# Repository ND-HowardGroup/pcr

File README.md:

ndPCR
=====

Historical code for ND PCR thermocycler, along with most current generation.

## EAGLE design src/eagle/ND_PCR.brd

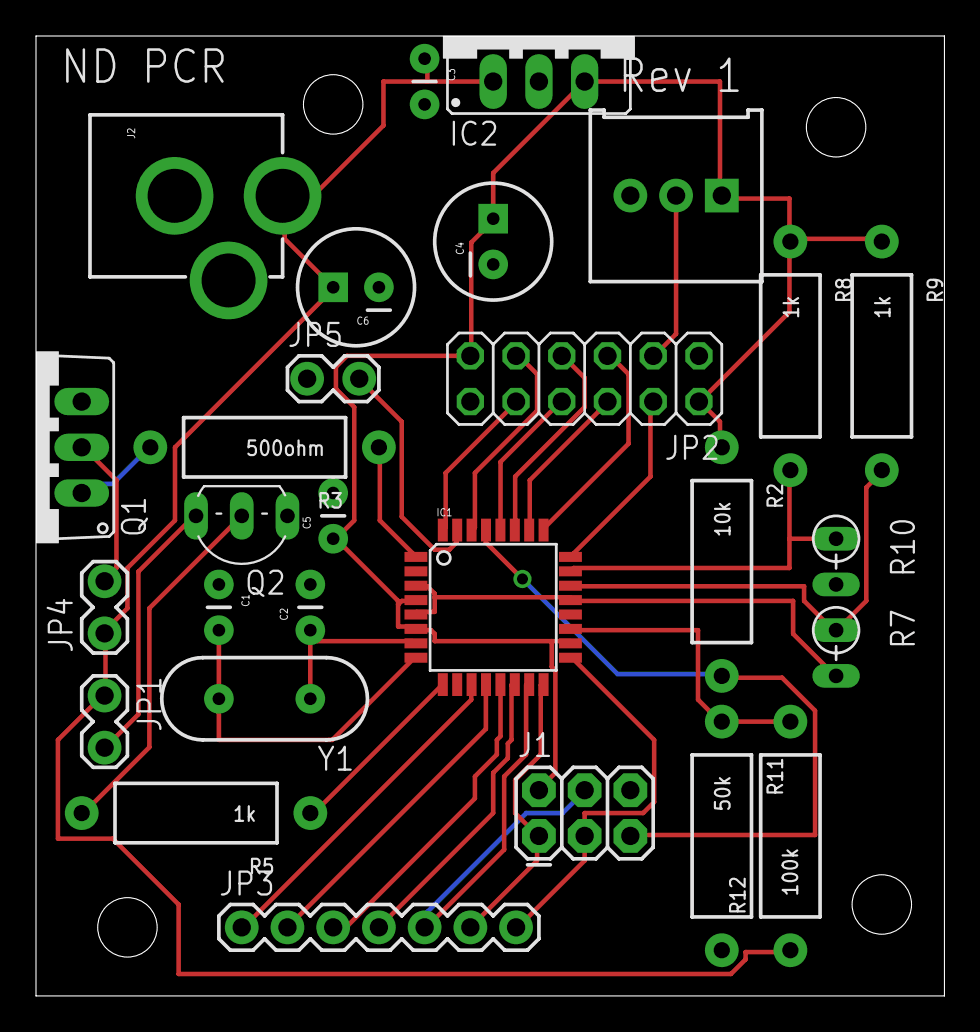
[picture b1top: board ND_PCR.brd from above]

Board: 2 copper layers, 50.5 x 53.3 mm, 32 parts (0 on the bottom side), 31 nets.

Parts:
C1, C2: 20 pF; CAP-PTH-SMALL
C3, C5: 100 nF; CAP-PTH-SMALL
C4, C6: 100 uF; CPOL-RADIAL-100UF-25V
IC1: AVR-MEGA8-AI; TQFP32-08
IC2: 7805; 78XXS
J1: ICSP; 2X3
J2: POWER_JACKPTH; POWER_JACK_PTH
JP1: Fan connector; 1X02_LOCK
JP2: LCD; 2X06
JP3: keypad; 1X07
JP4: 2x 27ohm in ||; 1X02_LOCK
JP5: serial out; 1X02_LOCK
Q1: TIP120TO220V; TO220AV
Q2: 2N2222TO92; TO92-EBC
R2: 10k; AXIAL-0.5
R3: 500ohm; AXIAL-0.5
R5, R8, R9: 1k; AXIAL-0.5
R7, R10: NTC2k; RS-2,5
R11: 50k; AXIAL-0.5
R12: 100k; AXIAL-0.5
R13: TRIMPOT-PTH-KNOB; 3386U
U$1, U$2, U$3, U$5: STAND-OFF
Y1: 16 MHz; HC49US

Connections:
GND: C1.1, C2.2, C3.2, C4.2, C5.2, C6.2, IC1.3, IC1.5, IC1.21, IC2.GND, J1.6, J2.GND, J2.GNDBREAK, JP2.1, JP2.12, JP5.1, Q1.E, Q2.C, R7.2, R10.2, R11.P$2, R13.3
unnamed: C2.1, IC1.7, Y1.1
unnamed: C1.2, IC1.8, Y1.2
unnamed: IC1.23, R8.P$2, R10.1
unnamed: IC1.15, J1.4, JP3.5
unnamed: JP4.2, Q1.C
unnamed: IC1.29, J1.5, R2.P$2
unnamed: IC1.16, J1.1, JP3.6
unnamed: IC1.17, J1.3, JP3.7
unnamed: IC1.24, JP2.4
unnamed: IC1.1, R3.P$1
unnamed: Q1.B, R3.P$2
unnamed: IC1.31, JP5.2
unnamed: IC1.22, R7.1, R9.P$2
unnamed: IC1.9, R5.P$1
unnamed: JP1.2, Q2.E
unnamed: IC1.26, JP2.6
unnamed: Q2.B, R5.P$2
unnamed: IC1.19, R11.P$1, R12.P$2
unnamed: JP2.3, R13.2
unnamed: IC1.25, JP2.5
unnamed: IC1.28, JP2.8
unnamed: IC1.27, JP2.7
unnamed: IC1.30, JP2.9
unnamed: IC1.32, JP2.10
unnamed: IC1.11, JP3.1
unnamed: IC1.12, JP3.2
unnamed: IC1.13, JP3.3
unnamed: IC1.14, JP3.4
V+: C3.1, C6.1, IC2.IN, J2.PWR, JP1.1, JP4.1, R12.P$1
VCC: C4.1, C5.1, IC1.4, IC1.6, IC1.18, IC2.OUT, J1.2, JP2.2, JP2.11, R2.P$1, R8.P$1, R9.P$1, R13.1

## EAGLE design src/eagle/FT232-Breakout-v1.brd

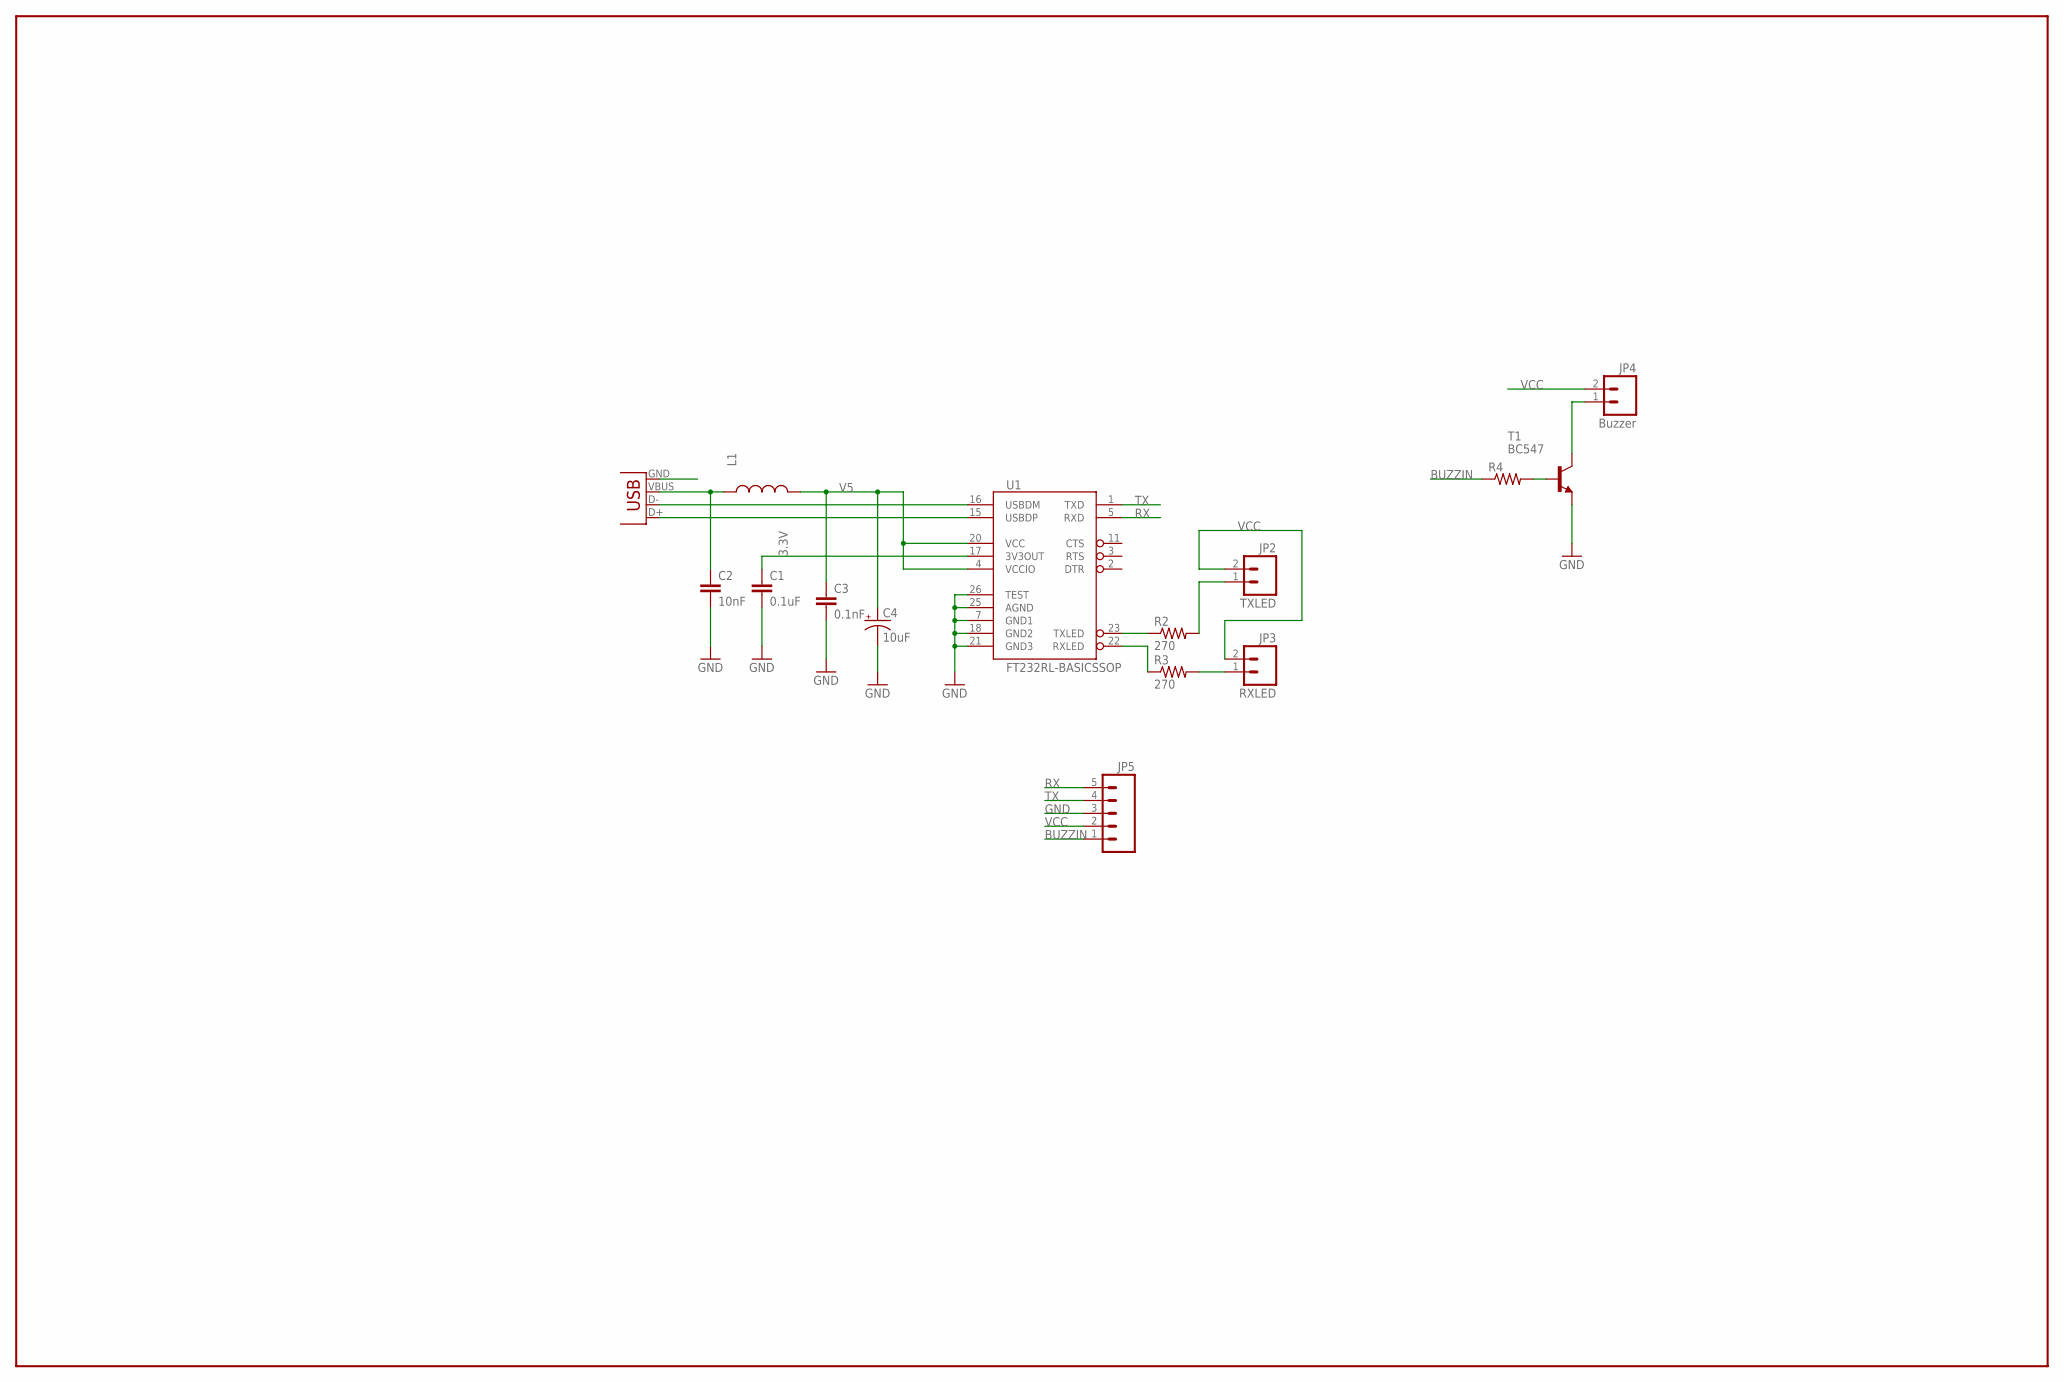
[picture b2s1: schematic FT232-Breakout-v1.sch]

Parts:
C1: 0.1uF; 0402-CAP
C2: 10nF; 0402-CAP
C3: 0.1nF; 0402-CAP
C4: 10uF; EIA3216
JP1: USB-B; USB-B-PTH
JP2: TXLED; 1X02_LOCK
JP3: RXLED; 1X02_LOCK
JP4: Buzzer; 1X02_LOCK
JP5: M05LOCK; 1X05_LOCK
L1: INDUCTOR0603; 0603
R2, R3: 270; AXIAL-0.5
R4: RESISTORPTH-1/2W; AXIAL-0.5
T1: BC547; TO92
U1: FT232RL-BASICSSOP; SSOP28DB

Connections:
3.3V: C1.1, U1.17 (3V3OUT)
BUZZIN: JP5.1, R4.P$1 (1)
GND: C1.2, C2.2, C3.2, C4.C (-), JP1.GND, JP5.3, T1.1 (E), U1.7 (GND1), U1.18 (GND2), U1.21 (GND3), U1.25 (AGND), U1.26 (TEST)
unnamed: C2.1, JP1.VBUS, L1.1
unnamed: R4.P$2 (2), T1.2 (B)
unnamed: JP3.1, R3.P$2 (2)
unnamed: JP1.D-, U1.16 (USBDM)
unnamed: JP1.D+, U1.15 (USBDP)
unnamed: JP4.1, T1.3 (C)
unnamed: R3.P$1 (1), U1.22 (RXLED)
unnamed: R2.P$1 (1), U1.23 (TXLED)
unnamed: JP2.1, R2.P$2 (2)
RX: JP5.5, U1.5 (RXD)
TX: JP5.4, U1.1 (TXD)
V5: C3.1, C4.A (+), L1.2, U1.4 (VCCIO), U1.20 (VCC)
VCC: JP2.2, JP3.2, JP4.2, JP5.2

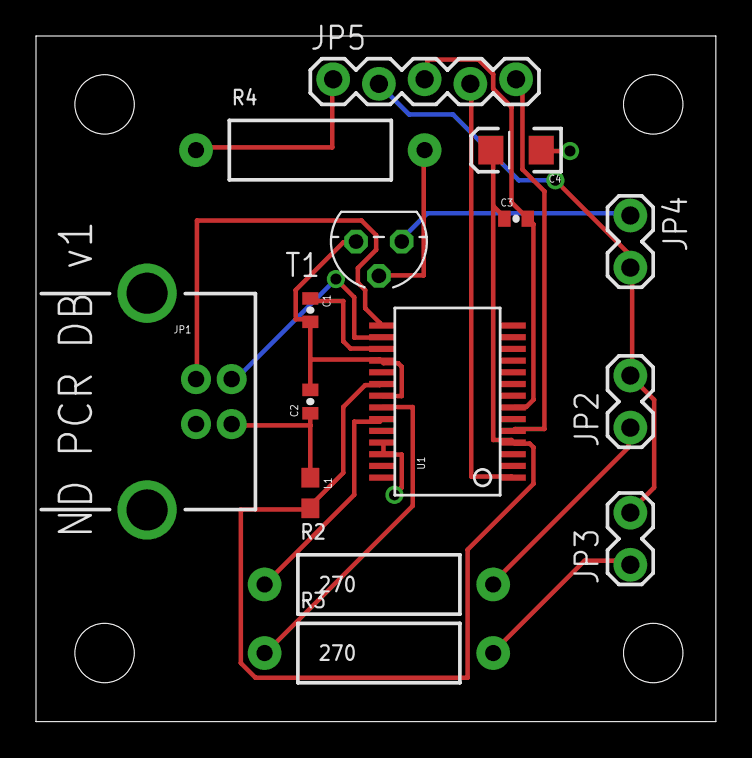
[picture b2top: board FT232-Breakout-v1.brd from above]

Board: 2 copper layers, 37.8 x 38.1 mm, 19 parts (0 on the bottom side), 16 nets.

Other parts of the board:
U$1, U$2, U$3, U$4: STAND-OFF

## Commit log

2012-06-11 renamed README.txt
2012-06-11 Added src and doc
2012-06-11 Update master
2012-06-14 demo of git
2012-06-14 demo of new folders
2012-06-14 Added CAD files for the case.
2012-07-18 added eagle schematics, cleaned up file names, moved cad/ to src/cad
2012-07-19 added libraries, more code, and AutoTune_PCR code
2012-07-19 added libraries
2012-07-20 test
2012-07-20 updated autotune file
2012-07-20 Updated PCR code
2012-07-20 New PID settings
2012-07-20 keypad library
2012-07-23 created function void readtemps() from ND_PCR to simplify
2012-07-23 corrected function readtemps() and changed the setting for the fan
    now, whenever output is < 10 the fan is turned on and the heater is
    turned off.
2012-07-23 Returned old fan setting
    the one i tried turned out to lock itself in a low temperature
2012-07-25 corrected readTemps()
2012-07-25 corrected temp
2012-07-25 use output from readTemps to control feedback in autotune
2012-07-25 deleted sign
2012-07-27 replaced 78l05 with 7805 in ND_PRC.brd
2012-08-01 change recipe #1 values
2012-09-17 added some labels
2012-11-06 First revision of code
2012-11-06 Third revision of code
    Includes desired output
2012-11-06 Fourth revision of code, includes LCD
2012-11-06 Revision 4.5 of code, fixing output to LCD
2012-11-06 Revision 4.5
    Now with more PID controller for heating elements
2012-11-06 Revision 5 with keypad input
    Takes input in at keypad level
2012-11-06 Revision 6, hardcoded recipes, select with keypad
2013-01-31 updated PCR schematic PDF
2013-03-06 Commit older versions and new version. New rev_7 includes full commenting, new PID tuning, better user interface, and stop buzzer. Still needs to include a buzzer pin and have code modified before bu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
2013-03-06 Commiting other files to ND PCR repository lost when I pushed all of my old code, in same hierarchy structure.
2013-03-06 Last commit removed everything, changing again. Sorry, I'm bad at Git.
2013-03-07 Added all old code to old repository, currently working in repo 7.
2013-03-07 Added all files moved to old folder.
2013-03-07 Commiting new folder structure.
2013-03-19 Changed alignment of text and headers. Fixed time remaining for the most part; it just adds a flat 7% to total time. Fixed display and some serial monitor display stuff. Added some more comments.
2013-05-21 demonstration of git
2013-05-30 added in additional enclosure design
2013-05-31 Implemented buzzer and changed test program to be able to end.
2013-08-19 frank's last changes
2013-08-19 always initialize varibles
2013-10-16 add daughter board
2013-10-16 modified daughter board for production
2013-11-13 demo for Gen
2013-11-13 Demo part 2
2014-07-24 PCR code fixes
    Changed recipe (times and temperatures) to match MTWASP from openPCR
    Added +2 degrees to offset temperature differences from sensed
    temperature in well vs temperature read by thermistors
    Fix serial print - now includes cycle number
    Measured rise and fall time and included in calcRemainingTime()
    Changed fudgeFactor to smaller value since rise and fall time are now
2014-07-24 Eagle CAD fixes
    Changed 10k resistor attached to thermistor voltage divider network to
    1k (1k provides broadest range for ADC on atmega328p)
2014-07-24 Main components datasheets
    Added datasheets and relevant application note for the main components
    on the NDPCR board for easy access
2014-12-16 Directory structure cleaned up and reorganized heavily. Bill of materials (BOM) generated through Eagle for both main and daughter boards. TODO lists added to src/ and doc/ folders. Deleted the USB_H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
2015-04-23 * Reorganized directory structure to build with 'ino' tool instead of Arduino IDE. * PCR code heavily modified and cleaned up. Keypad, buzzer, two fans, LCD display, and serial monitor is working. * 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
2015-04-23 ** ND-PCR v2 ready ** Reorganized directory structure to build with 'ino' tool instead of Arduino IDE. PCR code heavily modified and cleaned up. Keypad, buzzer, two fans, LCD display, and serial moni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
2015-04-29 Fixed the PCR recipes * Denaturation setpoint = 94 C * Final elongation time = 600 s

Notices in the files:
parts and their libraries:
SparkFun-DigitalIC: Licensing: CC v3.0 Share-Alike You are welcome to use this library for commercial purposes.
